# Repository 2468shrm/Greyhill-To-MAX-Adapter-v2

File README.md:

# Greyhill-To-MAX-Adapter-v2

Provides a solder-on PCB to a Greyhill 63R-series encoder. This terminates
with a SPARK MAX connector so that it could be used as an alternative to
a through bore encoder (from REV).

## Disclaimer

This board has not been fabricated and tested. It is published prior to
Kickoff to be compliant with FRC rules regarding fabrication schedule. But
the same rules would prohibit use of a functional prototype on a competition
robot, making it effectively e-waster. So I'll fab this after kickoff and
make updates if necessary.

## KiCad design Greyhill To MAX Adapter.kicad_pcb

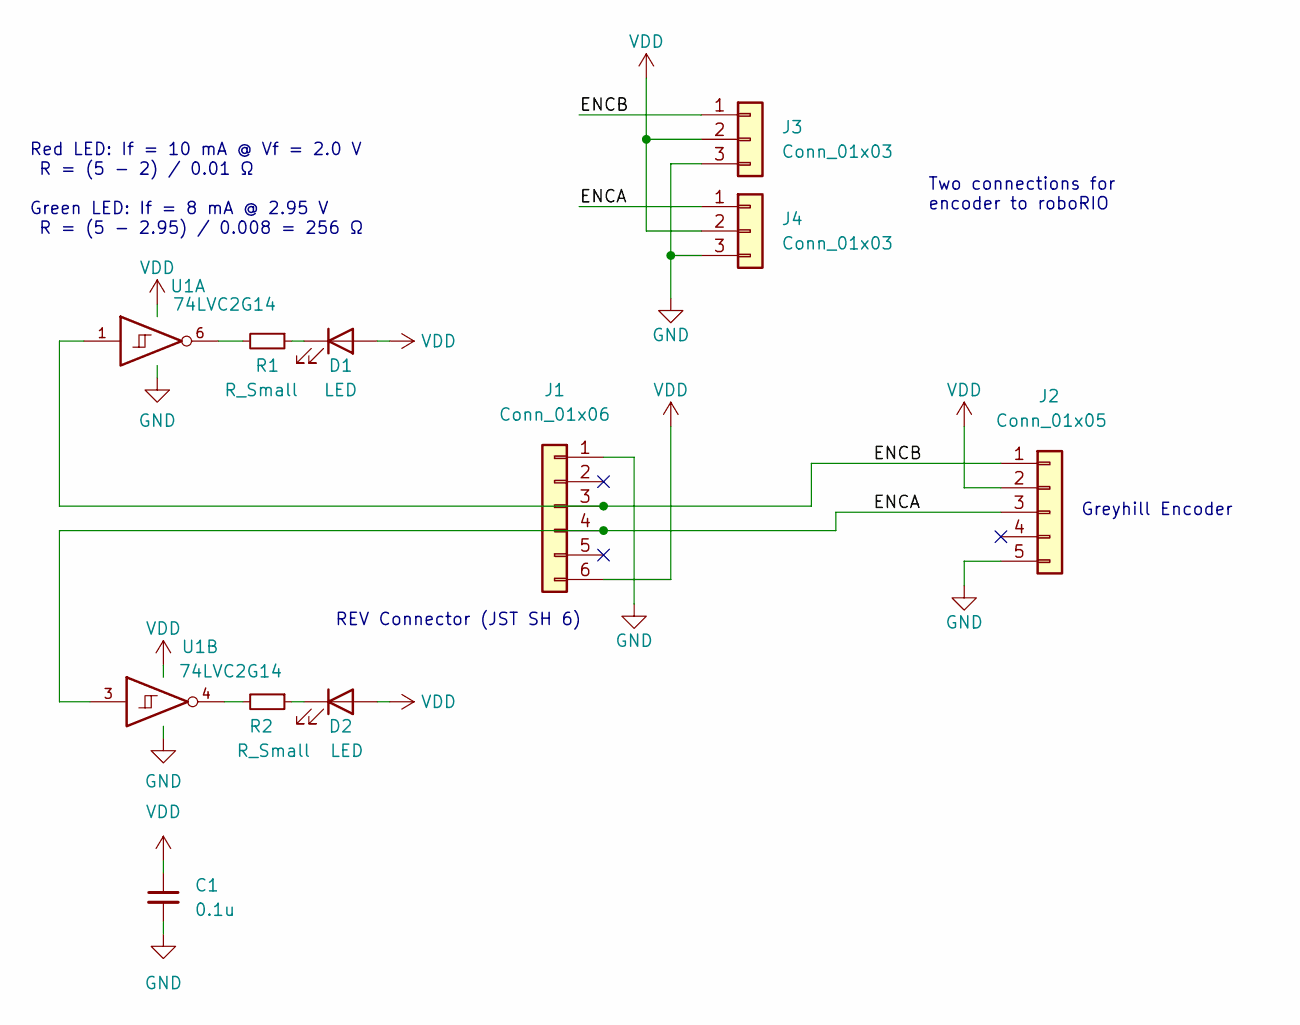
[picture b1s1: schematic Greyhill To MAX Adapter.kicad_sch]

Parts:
C1: 0.1u; C_0805_2012Metric
D1, D2: LED; D_1206_3216Metric
J1: Conn_01x06; JST_PH_B6B-PH-SM4-TB_1x06-1MP_P2.00mm_Vertical
J2: Conn_01x05; PinHeader_1x05_P2.54mm_Vertical
J3, J4: Conn_01x03; PinSocket_1x03_P2.54mm_Vertical
R1, R2: R_Small; R_0805_2012Metric
U1: 74LVC2G14; SOT-363_SC-70-6_Handsoldering

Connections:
/ENCA: J1.4, J2.3, J4.1, U1.3
/ENCB: J1.3, J2.1, J3.1, U1.1
GND: C1.2, J1.1, J2.5, J3.3, J4.3, U1.2 (GND)
unnamed: D1.1 (K), R1.1
unnamed: D2.1 (K), R2.1
unnamed: R1.2, U1.6
unnamed: R2.2, U1.4
VCC: C1.1, D1.2 (A), D2.2 (A), J1.6, J2.2, J3.2, J4.2, U1.5 (VCC)

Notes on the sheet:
REV Connector (JST SH 6)
Red LED: If = 10 mA @ Vf = 2.0 V R = (5 - 2) / 0.01 Ω Green LED: If = 8 mA @ 2.95 V R = (5 - 2.95) / 0.008 = 256 Ω
Greyhill Encoder
Two connections for encoder to roboRIO

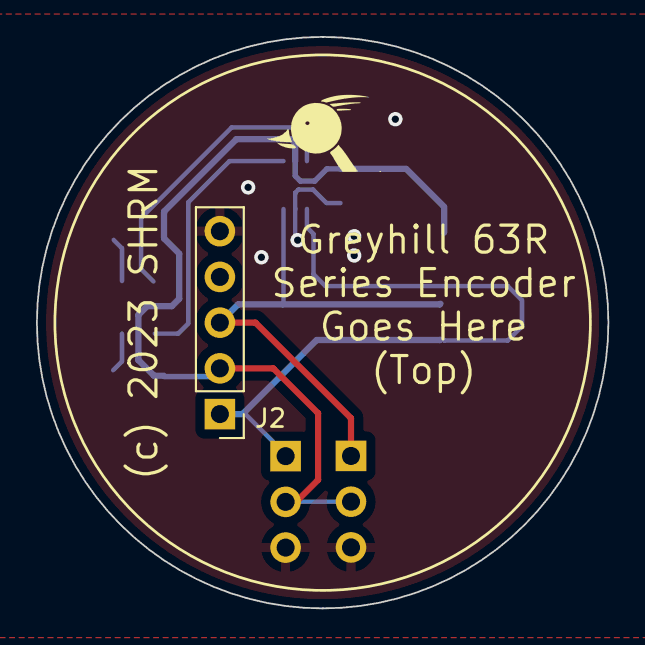
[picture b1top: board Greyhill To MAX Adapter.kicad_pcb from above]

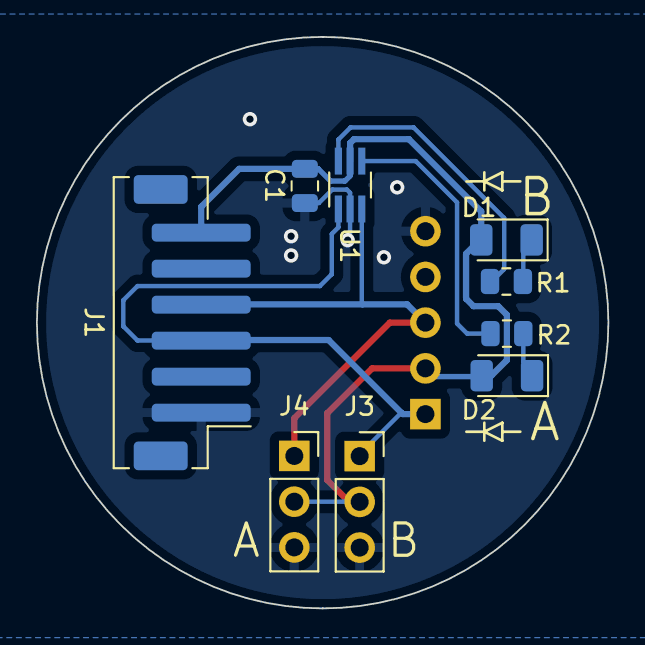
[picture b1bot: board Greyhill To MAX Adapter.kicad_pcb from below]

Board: 2 copper layers, 31.8 x 31.8 mm, 10 parts (9 on the bottom side), 8 nets.

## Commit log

2024-01-03 added PCB files
2024-01-03 updated docs

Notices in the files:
Greyhill To MAX Adapter.kicad_pcb:
(c) 2023 SHRM
